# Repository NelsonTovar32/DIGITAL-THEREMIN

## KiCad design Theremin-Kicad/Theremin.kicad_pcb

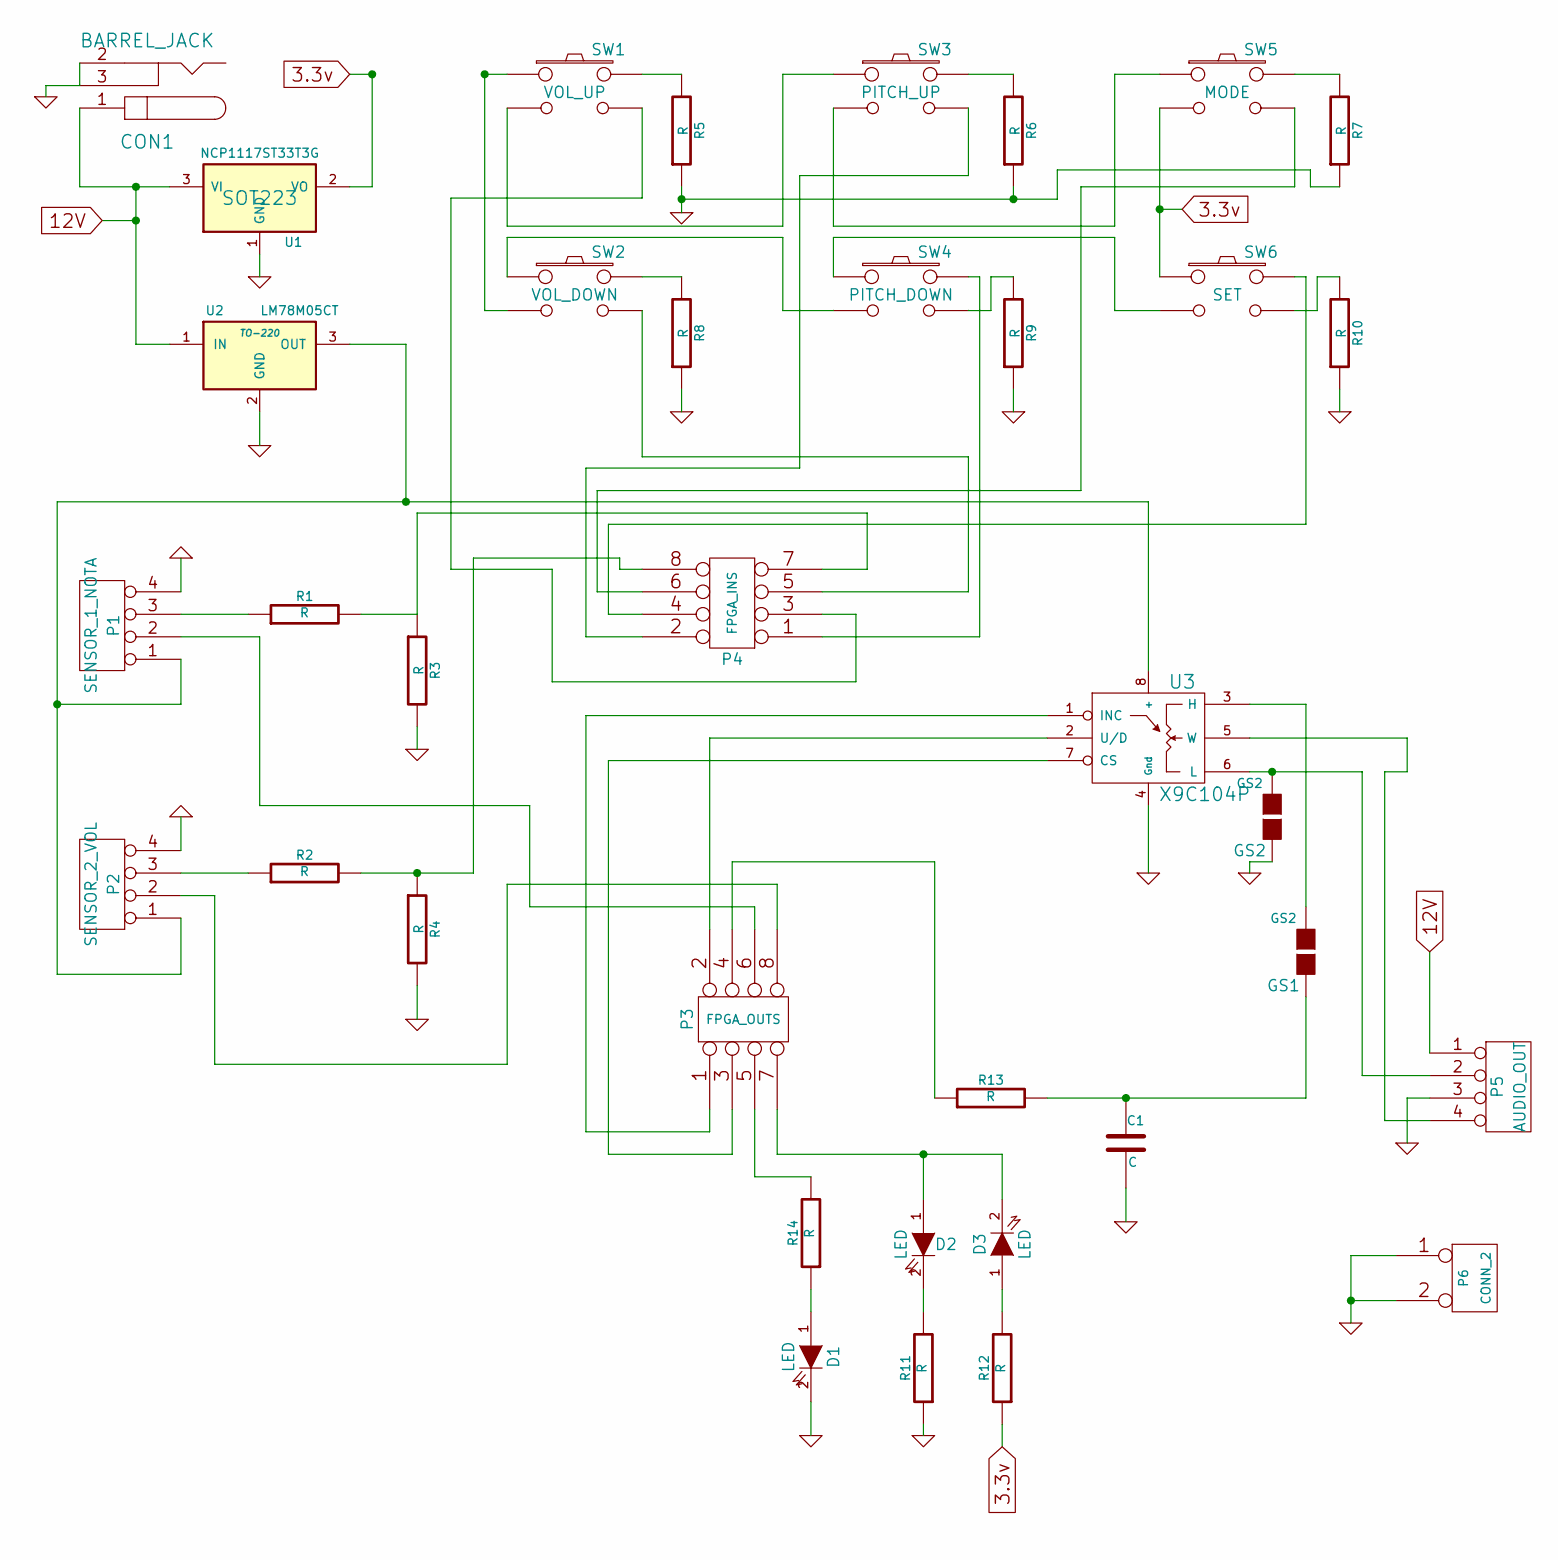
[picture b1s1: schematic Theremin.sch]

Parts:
C1: C
CON1: BARREL_JACK
D1, D2, D3: LED
GS1, GS2: GS2
P1: SENSOR_1_NOTA
P2: SENSOR_2_VOL
P3: FPGA_OUTS
P4: FPGA_INS
P5: AUDIO_OUT
P6: CONN_2
R1, R2, R3, R4, R5, R6, R7, R8, R9, R10, R11, R12, R13, R14: R
SW1: VOL_UP
SW2: VOL_DOWN
SW3: PITCH_UP
SW4: PITCH_DOWN
SW5: MODE
SW6: SET
U1: NCP1117ST33T3G; SOT223
U2: LM78M05CT; TO-220
U3: X9C104P

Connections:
3.3v: R12.1, SW5.3, SW6.1, U1.2 (VO)
12V: CON1.1, P5.1, U1.3 (VI), U2.1 (IN)
GND: C1.2, CON1.2, CON1.3, D1.2 (K), GS2.1 (G1), P1.4, P2.4, P5.3, P6.1, P6.2 (PM), R3.2, R4.2, R5.1, R6.1, R7.1, R8.1, R9.1, R10.1, R11.1, U1.1 (GND), U2.2 (GND), U3.4 (Gnd)
unnamed: P4.1, SW4.2
unnamed: P4.2, SW3.4
unnamed: R10.2, SW6.4
unnamed: R9.2, SW4.4
unnamed: SW1.1, SW2.3
unnamed: P3.4, R13.1
unnamed: P3.2, U3.2 (U/D)
unnamed: D2.1 (A), D3.2 (K), P3.7
unnamed: P3.5, R14.2
unnamed: D1.1 (A), R14.1
unnamed: P1.3, R1.1
unnamed: P2.3, R2.1
unnamed: P1.2, P3.6
unnamed: P2.2, P3.8
unnamed: R7.2, SW5.2
unnamed: R8.2, SW2.2
unnamed: SW2.1, SW4.3
unnamed: SW4.1, SW6.3
unnamed: SW3.3, SW5.1
unnamed: R6.2, SW3.2
unnamed: R5.2, SW1.2
unnamed: SW1.3, SW3.1
unnamed: P3.3, U3.7 (CS)
unnamed: P3.1, U3.1 (INC)
unnamed: P4.3, SW1.4
unnamed: P1.1, P2.1, U2.3 (OUT), U3.8 (+)
unnamed: P5.4, U3.5 (W)
unnamed: P4.5, SW2.4
unnamed: P4.7, R1.2, R3.1
unnamed: P4.4, SW6.2
unnamed: P4.6, SW5.4
unnamed: GS1.2 (G2), U3.3 (H)
unnamed: P4.8, R2.2, R4.1
unnamed: C1.1, GS1.1 (G1), R13.2
unnamed: GS2.2 (G2), P5.2, U3.6 (L)
unnamed: D2.2 (K), R11.2
unnamed: D3.1 (A), R12.2

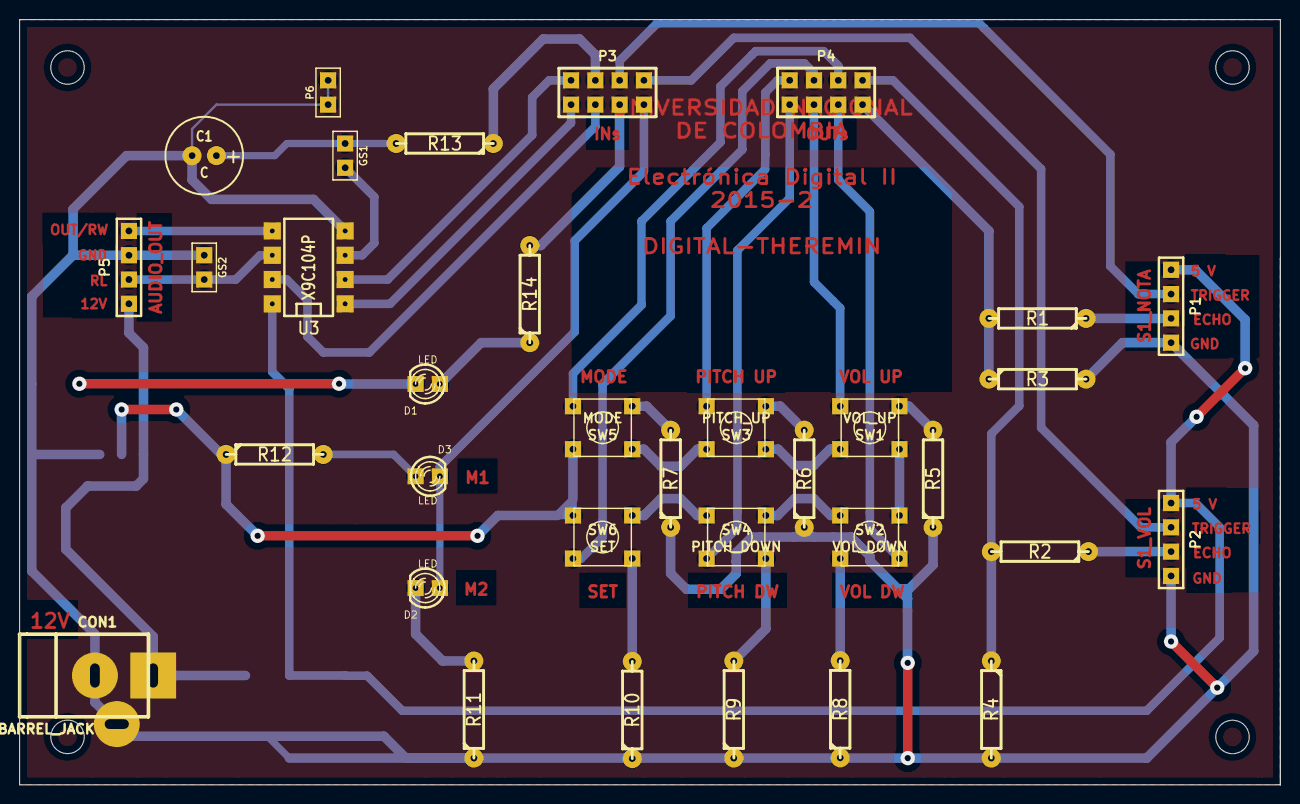
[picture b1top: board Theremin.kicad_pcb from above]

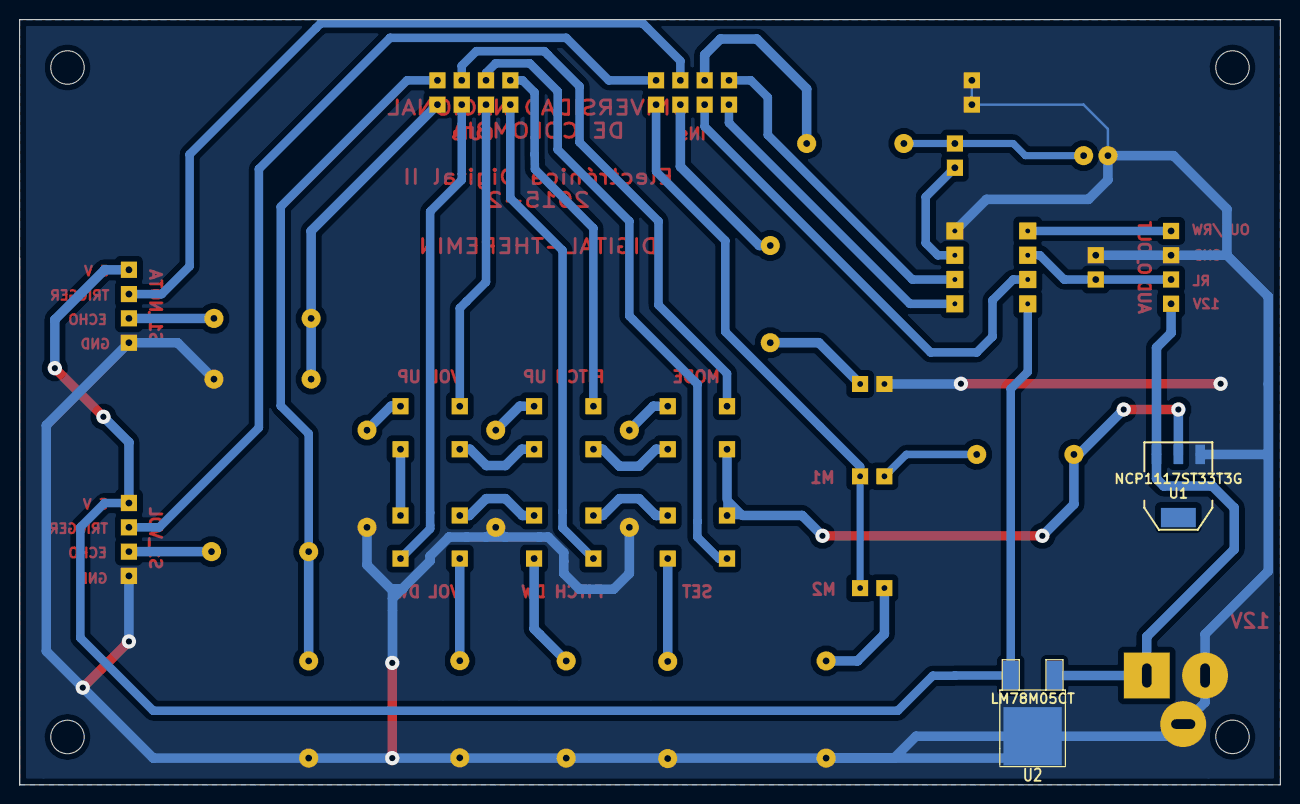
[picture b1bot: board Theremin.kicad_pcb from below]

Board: 2 copper layers, 131.8 x 80.0 mm, 36 parts (2 on the bottom side), 40 nets.

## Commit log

2015-10-21 actual
2015-10-21 actual2
2015-10-24 trigger correc
2015-10-27 26 Oct
2015-10-27 27 Oct
2015-10-31 30-Oct
2015-11-01 TestGit
2015-11-01 Revert "TestGit"
    This reverts commit b5cf4e9cd359b072b55eaad0666e52b744c69cea.
2015-11-01 Nov1:DIGPOT conectado
2015-11-01 1.Nov.DigpotConnect
2015-11-01 1.Nov.newCfunctions
2015-11-03 3 Nov
2015-11-04 Gpio Ferney
2015-11-04 entrega
2015-11-07 div_ajus_ok
2015-11-10 10 Nov
2015-11-15 Archivos PCB
2015-11-21 PCB Corregida
2015-11-22 PCB corregida2
2015-11-24 DIGPOT_OK
2015-11-25 25Nov
2015-11-27 Revert "25Nov"
    This reverts commit 00753210b0956ffd3ebe100875fb0ab7c5a08096.
2015-11-27 27Nov-PCB&PWM
2015-11-27 27Nov-Plots
2015-11-28 28Nov
2015-12-08 7Dic
2015-12-09 8Dic
2015-12-09 9dic
2015-12-09 ProyectoFInal
2015-12-11 10Dic
